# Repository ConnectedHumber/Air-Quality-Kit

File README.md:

# Air-Quality-Kit
Open source documentation and firmware for the CH HumberLora Kit

## Heltec Sensor V2

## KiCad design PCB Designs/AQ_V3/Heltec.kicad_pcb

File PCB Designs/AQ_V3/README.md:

# AQ_V3 PCB design

These are KiCAD files for the PCB design version 3. Historically V1 was based on a WeMOS device, V2 was based on a Heltec to enable the use of LoRa but had a track error.

V3 also incorporates a high side switch to allow the 5V to the SDS011 sensor to be turned off when the Vext is turned off. The GPS option (3V3) is also powered from the Vext. A large capacitor has been added to the 5V input to the Heltec to prevent resets caused by the SDS011 switching on.

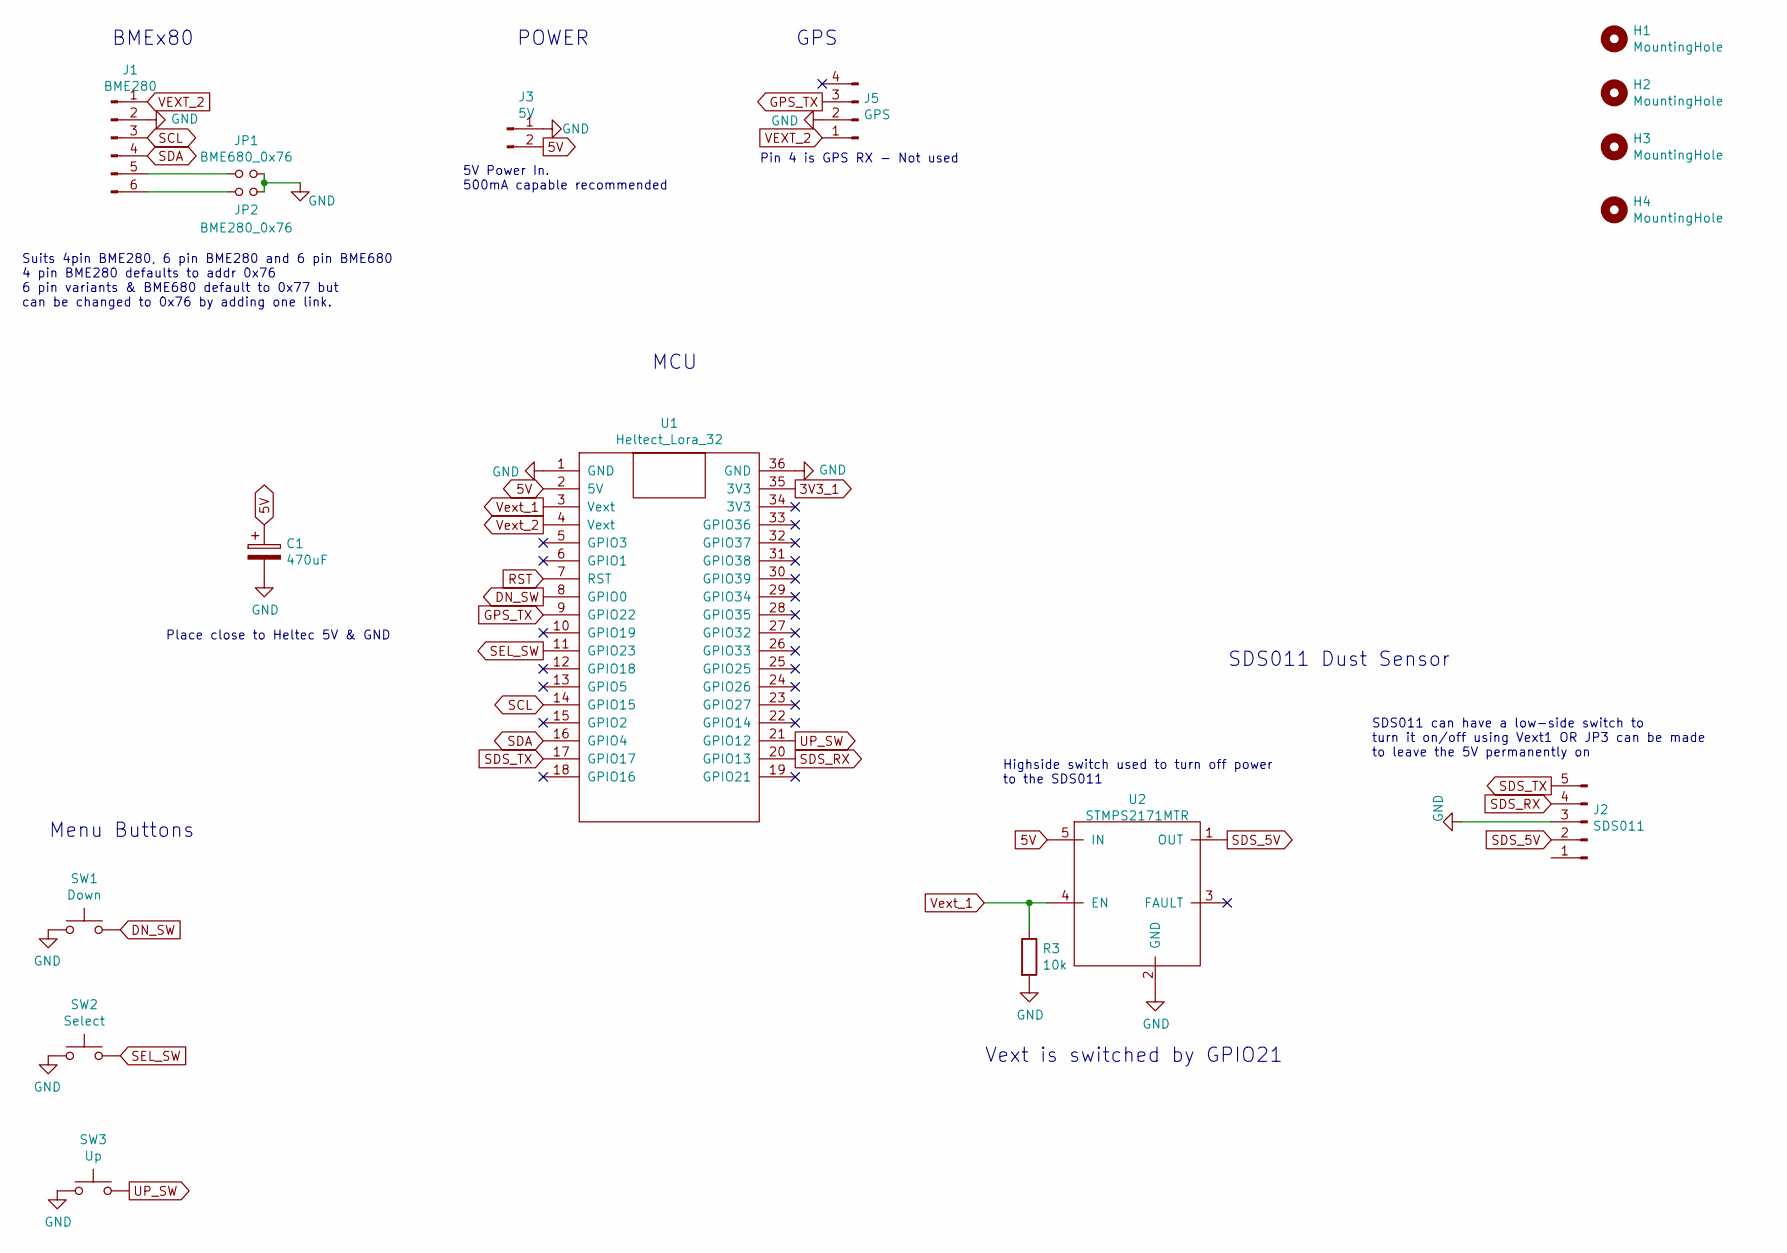
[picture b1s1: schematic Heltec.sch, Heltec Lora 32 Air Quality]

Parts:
C1: 470uF; CP_Radial_D6.3mm_P2.50mm
H1, H2, H3, H4: MountingHole; MountingHole_3.2mm_M3
J1: BME280; JST_XH_B06B-XH-A_1x06_P2.50mm_Vertical
J2: SDS011; JST_XH_B05B-XH-AM_1x05_P2.50mm_Vertical
J3: 5V; JST_XH_B02B-XH-A_1x02_P2.50mm_Vertical
J5: GPS; JST_XH_B04B-XH-A_1x04_P2.50mm_Vertical
JP1: BME680_0x76; SolderJumper-2_P1.3mm_Open_Pad1.0x1.5mm
JP2: BME280_0x76; SolderJumper-2_P1.3mm_Open_Pad1.0x1.5mm
R3: 10k; R_0805_2012Metric_Pad1.15x1.40mm_HandSolder
SW1: Down; SW_SPST_B3S-1000
SW2: Select; SW_SPST_B3S-1000
SW3: Up; SW_SPST_B3S-1000
U1: Heltect_Lora_32; Heltec_LoRa_32
U2: STMPS2171MTR; SOT-23-5_HandSoldering

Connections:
3V3_1: U1.35 (3V3)
5V: C1.1, J3.2, U1.2 (5V), U2.5 (IN)
DN_SW: SW1.1, U1.8 (GPIO0)
GND: C1.2, J1.2, J2.3, J3.1, J5.2, JP1.2, JP2.2, R3.2, SW1.2, SW2.1, SW3.1, U1.1 (GND), U1.36 (GND), U2.2 (GND)
GPS_TX: J5.3, U1.9 (GPIO22)
unnamed: J1.5, JP1.1
unnamed: J1.6, JP2.1
RST: U1.7 (RST)
SCL: J1.3, U1.14 (GPIO15)
SDA: J1.4, U1.16 (GPIO4)
SDS_5V: J2.2, U2.1 (OUT)
SDS_RX: J2.4, U1.20 (GPIO13)
SDS_TX: J2.5, U1.17 (GPIO17)
SEL_SW: SW2.2, U1.11 (GPIO23)
UP_SW: SW3.2, U1.21 (GPIO12)
VEXT_2: J1.1, J5.1
Vext_1: R3.1, U1.3 (Vext), U2.4 (EN)
Vext_2: U1.4 (Vext)

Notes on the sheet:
Place close to Heltec 5V & GND
Suits 4pin BME280, 6 pin BME280 and 6 pin BME680 4 pin BME280 defaults to addr 0x76 6 pin variants & BME680 default to 0x77 but can be changed to 0x76 by adding one link.
Pin 4 is GPS RX - Not used
SDS011 can have a low-side switch to turn it on/off using Vext1 OR JP3 can be made to leave the 5V permanently on
Highside switch used to turn off power to the SDS011
Menu Buttons
5V Power In. 500mA capable recommended
GPS
POWER
BMEx80
SDS011 Dust Sensor
MCU
Vext is switched by GPIO21

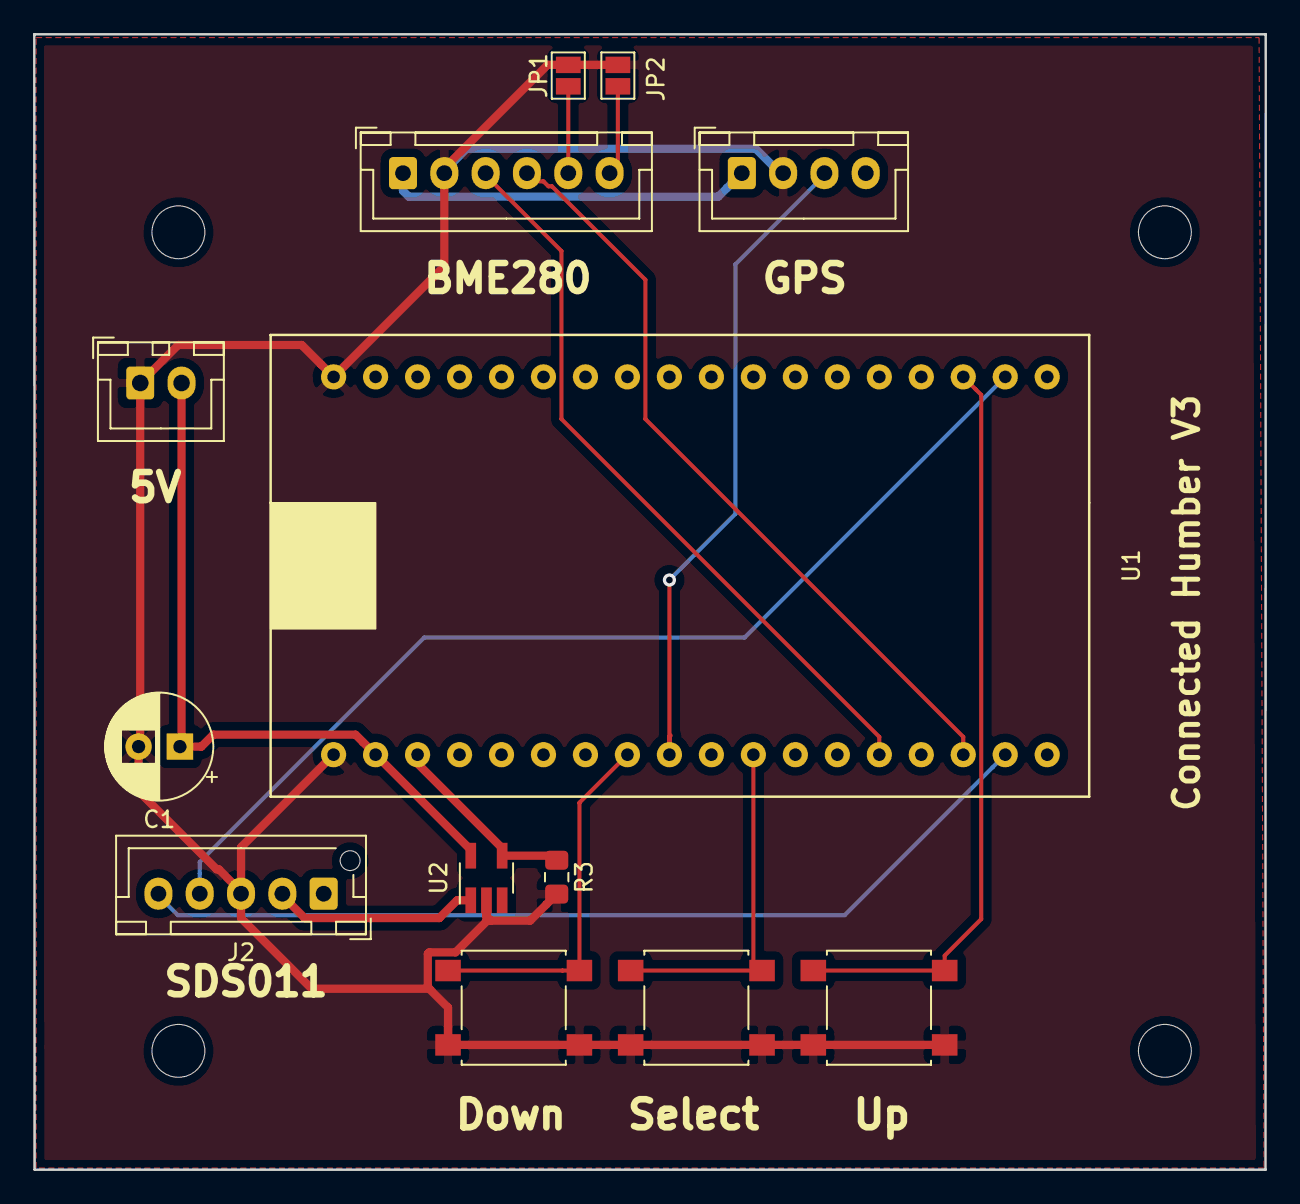
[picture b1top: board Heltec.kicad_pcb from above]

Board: 2 copper layers, 74.5 x 68.7 mm, 17 parts (0 on the bottom side), 15 nets.

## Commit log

2019-08-01 First commit
    original Author CrazyRobMiles
2019-08-01 First Commit
    Original Author: CrazyRobMiles
2019-08-01 First commit:
    Original Author: CrazyRobMiles
2019-08-01 Updated Contents Table
2019-08-27 Added built in filter to the plugs
    reduces BOM.
2019-08-28 first commit
    Requires part numbers adding - maybe
2019-08-29 Added enclosure mounting plate
    The plate is glued to the back of the enclosure therefore not requiring the enclosure to be drilled and so compromise its integrity.
2019-08-29 Plate to glue to back of enclosure for mounting
    Reduces risk of water ingress if used.
2019-08-29 Device Assembly
    Series of slides showing how to create the Connected Humber air monitoring device.
2019-09-09 BME280 and MQTT Fixes
    Added handling of secure sockets on MQTT port 8883. Improved BME280 to allow multiple I2C addresses .
2019-09-17 Added configuration commands document
2019-09-23 Heltec Sensor V2
2019-09-23 V3 PCB
2019-09-23 Added image of Heltec Sensor V2
2019-09-23 Finally go image to display
2019-10-04 Pre command upgrade
2019-10-04 Improved command decoder
2019-10-26 Explanation of JP1 and JP2 jumpers and PCB layout
2019-10-26 Upgraded menus and display timeout
2019-10-29 Fully featured with logging
2019-10-30 Logging options and string selection
2019-10-30 Popup issue fixed
2019-10-31 Fixed popup and sensor startup bugs
2019-11-02 Seems to work version
2019-11-03 First Migration of Top Hat code to ESP32
2019-11-03 Work in progress on V3
2019-11-05 Compiles and bits of it work.
2019-11-07 Even more of it works than last time
2019-11-09 Even workinger
2019-11-09 Fixed MQTT messages
    Fixed MQTT message format
2019-11-12 Added 3x10mm screw to secure antenna mounting and tidy up
2019-11-12 Added fixed popup messages
2019-11-17 Power switch tests
2019-11-17 Work in progress migrating settings into processors and sensors
2019-11-17 Still working on moving settings
2019-11-23 Refactoring work in progress
2019-11-23 Ongoing
2019-11-23 added test code
2019-11-27 Tidying up
2019-12-11 Added Cube stuff
2019-12-18 FireBeetle without timing
2019-12-23 build test
2020-01-09 First new sensor board releaed
2020-01-10 Lora device started working
2020-01-10 latest work in progress
2020-01-17 Working newboard
    Working new board code. Uses deep sleep between readings. Also disables brownout detector during power on of the 5V inverter.
2020-01-18 Latest nearly working version
2020-02-02 Working version
    Version prior to the addition of status flashing lights and WiFi failure management.
2020-02-02 Low Power Upgrade
    Added a messaging system and timeouts and shutdowns for WiFi and MQTT.
2020-02-05 It's a lot better now
    • Added stop methods to sensors.h, all the sensor drivers (airq, gps, bme280, clock) and modified sensors.c to connect them.
    • Updated the start and stop methods to improve the appearance of the display
    • added code to the BME280 to make it use the fitted value in settings
    • added settings for BME280 power pin and power control. Added code to use them in sensor startup and stop. This was a stupid idea. Power control should go in the power module.
    • Noticed that the BME280 initialise code seems to run OK when the sensor is not connected. If there is a BME280 connected it will give a "phantom response" when reset but return nan values. Can use 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
2020-02-05 Proper Power Management
    • removed the power settings from powercontrol and put them back into BME280 and particle sensor
    • converted powercontrol from a process into a library
    • create a structure that defines a switched power pin and added instances to BME280 and particle sensor. Added routines to manage the power pin.
    • Added a brownout detection specifier so that a pin can be controlled without causing brownouts.
    • Moved minimumPowerOffIntervalSecs into timing.c
    • added power pin particle sensor status management into the particle sensor code. Timing routines now just have to turn off the power and the particle sensor does the right thing.
2020-02-05 Nearly ready for release
    • Added handing of the LoRa settings to the web page
    • Tidied up the web page display and made the settings titles consistent
2020-02-06 Improved MQTT command management
    • fixed a bug whereby only the latest reading and not the average environmental values are sent in an MQTT reading. Fixed it.
    • changed the handling of timeout so that an incomplete reading is sent rather than just skipping a reading
    • Bug in modification so that the air quality reading was not sent when only the environmental sensor was disabled. This is because the reading age was less than the reading timeout. So a reading tak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
2020-03-24 added image
